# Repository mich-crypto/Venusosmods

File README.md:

# Venus OS mods: tank sensors and fridge for the camper van

Drivers that make devices Venus OS does not support show up as normal tanks
and temperature sensors in the Remote Console, on VRM, and on D-Bus (and so
on Modbus-TCP/MQTT):

| Device | D-Bus service(s) | Shown as |
|---|---|---|
| Mopeka Check **Standard / XL** (original, not Pro) | `com.victronenergy.tank.mopeka_standard` | LPG tank |
| Self-built **I/O extension** (ESP32-S3): hydrostatic fresh water sensor, grey tank rods, temperature probes | `com.victronenergy.tank.esp32_hydro`, `.tank.esp32_hydro_grey` (+ `.temperature.esp32_hydro_temp`, `.digitalinput.*` alarms) | fresh-water and waste-water tank (+ temperatures, frost / grey tank full alarms) |
| 12 V compressor **fridge** with the Alpicool Bluetooth controller (confirmed with a Hyckes dual-zone fridge) | `com.victronenergy.temperature.fridge_zone1` / `_zone2` | fridge / freezer temperature |

## Install (one command)

Open an SSH session to the Pi as `root` (the Termius app on an iPad works) and paste:

```sh
wget -qO- https://raw.githubusercontent.com/mich-crypto/Venusosmods/master/get.sh | sh
```

It downloads the mods, checks the Pi, switches on the **settings page** and prints its address and
password. Open that address on your phone, press **Unlock** and follow the **setup guide**: it finds your
gas sensor, fridge and I/O extension over Bluetooth, adds them to Venus OS and tells you where to find them.
Run the same command again any time to update; your settings are kept.

More: the [step-by-step guide](docs/GUIDE.md) (building the I/O extension, wiring, manual setup), also as a
printable **[PDF](docs/Venus-OS-Mods-Guide.pdf)**.

## Layout

```
data/                              -> copied to /data on the Pi
  shared_drivers/
    venus_service.py               shared layer: VenusDevice, TankDevice, TemperatureDevice, BleDriver
    ble_scanner.py                 passive BLE listener via BlueZ D-Bus (GLib loop, no bleak)
    ble_gatt.py                    BLE GATT client via BlueZ D-Bus (for the fridge)
    mopeka_std_parser.py           decoder: Mopeka Standard advertisements
    esp32_hydro_protocol.py        decoder: ESP32 advertisement (shared spec with the firmware)
    alpicool_protocol.py           decoder: fridge frames
    mopeka_venus.py                driver: Mopeka  -> tank
    esp32_hydro_tank.py            driver: ESP32   -> tank (+ temperature), Bluetooth check-in (Wi-Fi mode, firmware version)
    esp32_ota.py                   I/O extension firmware update from the Pi (Bluetooth, or HTTP on the van Wi-Fi)
    fridge_venus.py                driver: fridge  -> temperature per zone
    web_ui.py + web/index.html     settings page on port 8088: setup guide, calibration popups, drivers, dbus-serialbattery
    devices.py                     recognises Mopeka / fridge / ESP32 I/O extensions in a Bluetooth scan
    rawlog.py                      rolling log of the raw sensor bytes (shown on the Debug tab)
    starlink_hub.py                polls the dish, ping, speed tests, WAN IP, Telegram sending
    notifier.py                    Telegram notifications: battery, alarms, geofence, frost, Orion XS
    netmon.py                      energy, data use, outage and test bookkeeping (JSON store)
    starlink.py                    Starlink dish status (gRPC-web, hand-made protobuf reader)
    battery_debug.py               battery history for the graphs (cells, current, temperatures)
    config_tools.py                config.ini parsing, validation and safe writing for the page
    diagnostics/
      test_venus_compatibility.py  read-only pre-flight check, PASS/WARN/FAIL, optional BLE scan
      fridge_probe.py              does my fridge speak the supported protocol?
      starlink_probe.py            does the Starlink dish answer, and do we understand it?
    config.ini.example
    install.sh / uninstall.sh
  etc/init.d/<service>/run         daemontools services (+ log/run)
firmware/esp32_hydro_tank/         Arduino sketch for the ESP32-S3 (calibration via serial or its own Wi-Fi page)
firmware/bin/                      ready-made firmware for the browser flasher and the page's update
tools/tank_table.py                height->litres table from tank dimensions
tools/tank_wheelarch.py            filling chart of the wheel-arch tank (docs/tank/tank-drawing.jpg)
docs/                              guide, wiring, calibration
tests/                             unit tests + D-Bus integration test with simulated sensors
```

The layers are separate. Parsers (pure Python, no D-Bus) turn bytes into
readings. Devices publish one Victron D-Bus service each. Drivers connect
the two, one process per sensor. A new sensor type needs a parser and a
small driver; everything else is shared.

## Design decisions and review points

| Topic | How it is handled |
|---|---|
| Mopeka Standard | `mopeka-iot-ble` only decodes the Pro series. The Standard (company id 0x000D) decoder is a port of ESPHome's `mopeka_std_check`. |
| asyncio vs GLib | No bleak. BlueZ publishes advertisements and GATT on the system D-Bus, so everything runs in the GLib loop vedbus needs. No threads, no `pip install`, survives Venus OS updates. |
| Units | Config in litres. D-Bus `/Capacity` and `/Remaining` in m³ (60 L → 0.06), `/Level` in %. |
| Fluid types | Victron enum: 0 fuel, 1 fresh water, 2 waste water, 5 black water, 8 LPG, 11 raw water. |
| Metadata | velib_python `add_mandatory_paths` (Mgmt/*, DeviceInstance, ProductId, ProductName, Connected...), `/CustomName`, `/Status`. Each service is registered only after all its paths exist (`register=False` + `register()`). |
| Device instance | Stored in localsettings `/Settings/Devices/<id>/ClassAndVrmInstance`, which also resolves clashes. Stable across reboots, changeable in the GUI. |
| Several services | Each service has its own private D-Bus connection (vedbus object paths are per connection) and a unique, stable name from config. |
| velib path | Searched in `ext/velib_python`, `dbus-systemcalc-py` and `/opt/victronenergy/*/ext/velib_python`. The diagnostics report which one is used. |
| Sensor health | Per-device last-seen time. After `timeout`: `/Connected` = 0, `/Status` = disconnected, values set to invalid. Recovers on the next valid reading. Sensor faults show as `/Status` error, never as "empty". |
| Temperature | The tank `/Temperature` path is documented for Mopeka only, so the ESP32 water temperature is optionally also published as its own `com.victronenergy.temperature` service. DS18B20: CRC is checked, 85 °C power-on values are rejected, and the value is dropped after 3 bad reads. |
| Shutdown | SIGTERM (`svc -d`) is handled: the fridge connection is closed cleanly. |
| Persistence | Services in `/data/etc/init.d`, linked into `/service` and re-linked at boot by `/data/rc.local`. |
| Config format | INI rather than JSON: it can have comments and is easier to edit with `nano` over SSH. Checked by the diagnostics (MAC format, unique services, value types). |
| Non-square tank | Height→litres table measured by filling in steps (serial commands, stored in ESP32 flash) or calculated from dimensions with `tools/tank_table.py`. |

## Tests

```sh
python3 -m unittest discover tests -v
```
These test the decoders (including frames captured from real fridges) and the
driver logic with fake D-Bus objects, so they run on any PC.

`tests/integration_dbus.py` runs all three real drivers with the real
velib_python on a private D-Bus. A fake BlueZ sends Mopeka/ESP32
advertisements and plays a dual-zone fridge over GATT, and the test checks
every published value plus the clean shutdown:
```sh
git clone https://github.com/victronenergy/velib_python /tmp/velib_python
VELIB=/tmp/velib_python dbus-run-session -- python3 tests/integration_dbus.py
```

The firmware compiles warning-free on Arduino-ESP32 2.0.17 (Bluedroid) and
3.3.x (NimBLE).

Verified on the real installation (Venus OS 3.79, Raspberry Pi): the
diagnostics, Mopeka Standard decoding, and reading a Hyckes dual-zone fridge.
On the Pi's built-in Bluetooth, a GATT connection fails ("Busy") while any
process scans, so the fridge driver pauses the other drivers' scanning for
its few seconds of each read (`/tmp/venusosmods-ble-pause`). Still to verify:
the GUI/VRM display, and the ESP32 sender once it is built.

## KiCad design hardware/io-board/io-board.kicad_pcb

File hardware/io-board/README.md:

# I/O board – KiCad project (rev 0.4, routed, audited, JLCPCB parts – prototype)

KiCad 7 project for the board described in [docs/io-board.md](../../docs/io-board.md) and
[docs/io-board-schematic.md](../../docs/io-board-schematic.md). Open `io-board.kicad_pro` in
KiCad 7 or newer.

| File | What |
|---|---|
| `fab/io-board-gerbers.zip` | **Send this to the board maker:** Gerbers (2 layers, mask, paste, silkscreen, outline) and Excellon drill files (PTH and NPTH separate) |
| `fab/jlc/io-board-bom-jlc.csv`, `fab/jlc/io-board-cpl-jlc.csv` | **JLCPCB assembly files:** BOM with LCSC part numbers and placement list (164 parts; U92 not fitted), see "Ordering at JLCPCB" |
| `fab/io-board-pos.csv` | KiCad pick-and-place file (165 parts incl. U92, all on top; fiducials excluded) |
| `fab/io-board-bom.csv`, `io-board-bom.csv` | Parts list grouped by value and footprint (165 parts incl. U92; net ties, fiducials and the JP10 solder jumper are copper only) |
| `io-board.kicad_pcb` | Board 120 × 140 mm, 2 layers, **fully routed**: 0 unconnected, 0 DRC errors (see Checked) |
| `io-board.kicad_sch` | Schematic: 170 symbols (165 parts, the JP10 solder jumper, 4 net ties), grouped in 7 sections (power, ESP32, EBL, tanks, outputs, Truma + inputs, USB PD + sensors + expansion) |
| `io-board-schematic.pdf` | The schematic as PDF |
| `io-board.net` | Netlist exported by KiCad |
| `io-board.dsn` | The unrouted board for Freerouting (with the net classes) |
| `pcb-render-top.png`, `pcb-render-bottom.png` | Renders of the bare board as it comes from the fab (`sh tools/render.sh`) |
| `HANDOVER.md` | State, open items, tool chain and pitfalls for the next working session |
| `DESIGN-REVIEW.md` | Independent design audit: findings, calculations, what is and is not verified |
| `io_board.kicad_sym`, `sym-lib-table` | Project library with the PCA9615 symbol (not in the KiCad library) |
| `io_board.pretty`, `fp-lib-table` | Project footprints: RJ12 Connfly DS1133-S60 (6P6C), SK6812MINI-HS |
| `tools/` | Scripts: generate schematic and board from `parts.py`, rules, routing import, finishing, BOM, fab files |

**Order:** 2 layers, 1.6 mm FR-4, 1 oz (35 µm) copper, min. track/gap 0.15 mm, min. drill 0.3 mm,
any solder mask colour, **ENIG** finish (flat pads for the LGA-16, DFN-4 and 0.5 mm parts),
one internal routed slot (1 mm, around the SHT40).

## Checked

* **DRC (KiCad 7, with the KiCad libraries): 0 errors, 0 unconnected pads.** 38 warnings remain,
  all accepted: 31 × silkscreen past the board edge (the pluggable terminal blocks, RJ sockets,
  front-edge buttons and the ESP32 antenna overhang on purpose), 5 × the small J5 pin names touch
  the D1/D4 outline, 1 × silkscreen over a pad (removed in the Gerbers), 1 × ESP32 footprint
  differs from the library (thermal vias 0.3 mm, the 2-layer fab minimum).
* **Every pad carries the net `tools/parts.py` gives it** (525 pads compared), every footprint is
  linked to its schematic symbol, JLCPCB BOM and placement list agree (164 parts).
* KiCad reads the schematic and exports the netlist: 170 components, 120 named nets; the only
  one-pin nets are pins left open on purpose (spare ESP32 pins, sensor pins not used, SBU, LED DOUT).
* Electrical rules checked on KiCad's netlist: no two outputs on one net, every power input fed
  (power flags on GND, V12_SYS, V12_AUX, LIN_VBAT and the supplies).
* All footprints are linked to their symbols (Tools → Update PCB from Schematic works).
* No footprints overlap; all inside the outline (the ESP32 antenna keep-out sits at the back edge).
* Silkscreen: only small reference designators (placed so none overlaps a pad or another text),
  pin names next to every terminal block (J5: AUX+, GND, CP+, GND; J11: O1 C/NO/NC;
  J12: O2 C/NO/NC; J10: COM, IN1–IN3); part values are on the Fab layer only.
* KiCad 7's command line has no ERC: run **Inspect → Electrical Rules Checker** once in the GUI
  if you change the schematic.

## Before ordering

1. **Truma RJ12:** confirm pin 3 = LIN, pin 5 = GND with a meter; use a 1:1 cable.
2. **PCA9615 pinout:** checked against the NXP datasheet (Rev. 2, Table 3) and corrected (see below).
3. **Connector orientation:** all connectors open towards the edge they sit on (J5, J11, J12
   left; J8, J9, J3, J10 right; J1, J4, J6, J7 front). **J8/J9 (RJ12) use a footprint derived from
   KiCad's RJ14 Connfly DS1133** (6 contacts instead of 4): compare it with the Connfly drawing
   (LCSC C77859) – if the contact stagger were mirrored, LIN would arrive on pin 4.
4. **Front plate parts:** the 12 V ON/OFF buttons (Alps SKHHLQA010, right-angle, 8.35 mm stem,
   about 3 mm past the board edge) reach through holes in the front plate; the green "12 V on"
   LED (0603) and the RGB status LED sit at the edge and need light pipes in the plate.
5. **USB-C tablet charging:** a ready-made 12 V → USB-C PD 30 W module on J2 (its socket in the
   front plate), switched by Q80; no PD chip on this board.
6. **Tilt sensor:** order the **LIS3DH** (LGA-16 3 × 3, as on the board). The LIS2DH12 is LGA-12
   2 × 2 and does not fit this footprint.
7. **Stock:** JLCPCB stock was checked on 2026-11-28 (numbers in `tools/lcsc.py`); the BOM upload
   shows any line that ran out. U92 (PCA9615) is not fitted – solder it later for expansion boards.
8. **Plugs:** the pluggable terminal blocks need their plugs (not assembled): 1 × KF2EDGK-5.0-4P
   (C440871), 2 × KF2EDGK-5.0-3P (C440870), 1 × KF2EDGK-3.5-4P (C440849) – order from LCSC.
9. Order one prototype first.

## Ordering at JLCPCB

1. **PCB:** upload `fab/io-board-gerbers.zip`. 2 layers, 1.6 mm, 1 oz, **ENIG**, any colour; the
   board has one internal routed slot (SHT40) – JLCPCB detects it from the outline.
2. **Assembly:** "PCB Assembly", top side, **Standard** PCBA (the board has through-hole parts:
   relays, terminal blocks, RJ sockets, Micro-Fit, TSR-1, buttons). Upload
   `fab/jlc/io-board-bom-jlc.csv` and `fab/jlc/io-board-cpl-jlc.csv`.
3. **Check the placement preview** part by part, especially the rotation and pin 1 of: U3
   (ESP32), U90 (LIS3DH), U91 (SHT40), U60, U5–U8/U71–U73 (opto/photoMOS), D1–D4,
   D13, D14, D61, the LEDs and the RJ/USB connectors. The CPL uses KiCad's rotations; JLCPCB
   corrects them in the preview where their library differs.
4. Confirm the parts JLCPCB marks as "extended" (one-off fee per part type) and the through-hole
   parts (soldering fee).

## Checked against datasheets

Pinouts read from the manufacturers' datasheets (NXP PCA9615 Rev. 2, Diodes AP7361C, AOS AO3401A,
TI INA180 SBOS741H, Omron G5LE, SK6812MINI-E Rev. 02) and from KiCad's library symbols.

**Fixed:**

| Part | Problem | Fix |
|---|---|---|
| U92 PCA9615 | Pins 2–9 were wrong: pin 5 (VSS) was on +3.3 V, SDA/SCL/EN and the differential pins swapped | Pinout per Table 3: 1 VDD(A), 2 SDA, 3 EN, 4 SCL, 5 VSS, 6 DSCLM, 7 DSCLP, 8 DSDAP, 9 DSDAM, 10 VDD(B) |
| U2 AP7361C-33E | "-33E" is the SOT223 package; the board had a SOT-89-3 footprint (the SOT89 version has 5 pins) | Footprint SOT-223-3 (tab = GND) |
| Q80 AO3401A | Gate rated ±12 V, but Q81 pulled it to GND: VGS = −12…−14.6 V | R83 100 k in series: VGS = −V/2 (≈ −7 V), RDS(on) < 60 mΩ at −4.5 V |
| D5 status LED | Value SK6812MINI-E (3.2 × 2.8, pin 1 VDD, 4 DIN) on the SK6812MINI footprint and pinout (3.5 × 3.5, pin 4 VDD) | Value SK6812MINI, to match footprint and pinout |
| D5 data level | SK6812MINI: VIH 3.4 V at VDD 5 V (datasheet); the ESP32 drives 3.3 V | LED fed through D6 (1N4148W): VDD ≈ 4.3 V, VIH ≈ 2.9 V (scales with VDD) |
| D4 TVS | SMBJ24CA clamps at 38.9 V, above C1 (35 V) and the TSR-1 input (36 V) | SMBJ18A (stand-off 18 V, clamps 29.2 V), band to V12_SYS |
| R50/R51 shunts | 0.05 Ω at 5 A = 1.25 W; a standard 2512 is 1 W | Value "0.05 2W" (2 W or 3 W metal strip 2512) |
| U90 | BOM said LIS2DH12, which does not fit (see 6.) | Value LIS3DH |

**Verified, no change:** INA180A3 (pinout A: 1 OUT, 2 GND, 3 IN+, 4 IN−, 5 VS; common mode up to
26 V), G5LE-1 (coil 2–5, COM 1, NO 3, NC 4; 8 A at 30 VDC against 5 A used), TJA1021T, USBLC6-2SC6,
SHT40, LMV331, AO3400A, TSR 1-2450 (KiCad symbols). No mains voltage on the board: the EBL "mains"
wire is an ≈ 8 V indicator, so no high-voltage clearances are needed.

**Still for you to check (not possible from here):**

* **Stock:** see Before ordering, 7.
* **Pressure sensor:** the ADC input has no divider, so it is for the 0–3.3 V sensor (QDY30A). A
  0.5–4.5 V sensor needs a divider at R21/R22.
* **AO3401A turn-off:** R80/R83 make Q80 switch slowly (100 k); fine for the PD module, not for PWM.

## Rev 0.4: parts JLCPCB stocks

Every part is now one JLCPCB/LCSC stocks (2026-11-28); the substitutes and the fixes found
while reading their datasheets:

| Ref | Rev 0.3 | Rev 0.4 (LCSC) | Notes |
|---|---|---|---|
| K1, K2 | Omron G5LE-1 12 V (no stock) | Songle SRD-12VDC-SL-C (C30431) | 10 A 250 VAC / 28 VDC; same pin functions (1 COM, 2–5 coil, 3 NO, 4 NC), SRD footprint |
| J5 (10-way push-in) | Phoenix PT 1,5 | J5 4-way (AUX+, GND, CP+, GND), J11 / J12 3-way (output 1 / 2 C, NO, NC): pluggable KF2EDGR-5.0 (C441195, C441194) | 15 A; plugs ordered separately |
| J10 | Phoenix PT 1,5 3.5 mm | KF2EDGR-3.5-4P (C441173) | pluggable |
| J8, J9 | Amphenol RJ12 | Connfly DS1133-S60BPX (C77859) | footprint derived from KiCad's DS1133 RJ14 – check (Before ordering 3) |
| J3 | Amphenol RJ45 | Connfly DS1128-09-S8B8S (C77851) | shielded, shield to GND |
| F2, F4, F5, F7 | blade holder / 1812 fuses | Littelfuse Nano2 0451010/005/004 (C44479, C48467, C27515) | soldered SMD fuses, 125 V |
| SW1, SW2 | TL3342 | XKB TS-1187A-B-A-B (C318884, basic) | |
| SW3, SW4 | PTS645VL83 | Alps SKHHLQA010 (C125034) | right-angle, 8.35 mm stem |
| D9 | 3 mm right-angle LED | green 0603 (C12624) at the front edge | light pipe |
| D5 | SK6812MINI (no stock) | SK6812MINI-HS (C2922787) | **different pin positions** – own footprint from the OPSCO pad drawing |
| JP1, JP2 | 0 Ω 2512 | 1 mΩ 2 W 2512 (C2904226) | 44 A rated |
| C1 | 47 µF 35 V 1210 | 10 µF 50 V X7R 1210 (C138687) | |
| Q3 | IPD90P04P4L-04 (no stock) | AOS AOD4185 (C400894) | −40 V, 15 mΩ: 0.4 W at 5 A, 1.5 W at 10 A (RθJA 50 °C/W) |
| U92 | PCA9615 (no stock) | **not fitted** | termination and ESD stay; fit for expansion boards |
| **U5, U6** | AQY212EH on SO-4 footprint | **SMDIP-4** footprint | **error since rev 0.1:** the AQY212EH is a DIP4 part; its SMD version (EHAX, C29276) has gull-wing leads |

Also: pin names of the left terminal blocks turned 90° between the blocks and the relays;
`finish_routes.py` now routes wide nets first, never makes a pad stub narrower than the pad
allows, and respects pads' own clearances (fiducials).

## Rev 0.3: audit findings fixed

The independent audit ([DESIGN-REVIEW.md](DESIGN-REVIEW.md)) found three HIGH and six MEDIUM
issues in rev 0.2. All are resolved in rev 0.3 and re-measured on the routed board:

| Finding | Fix in rev 0.3 | Re-measured |
|---|---|---|
| H1 decoupling 15–109 mm from the pins, no bypass at INA180/LMV331 | Capacitors placed by a near-pin rule (`NEAR` in `pcb.py`); C9 (TSR-1 out), C94–C97 (INA180/LMV331) added | every decoupling cap 2.1–4.5 mm from its pin |
| H2 12 V AUX without reverse-polarity / transient protection | Q3 IPD90P04P4L-04 P-MOSFET (D13 12 V gate clamp, R7) after F2; D14 SMBJ15A on V12_AUX | reversed AUX: Q3 off; clamp 24.4 V < INA180 26 V, < 30 V MOSFETs |
| H3 front-plate controls behind the plugs | Right-angle buttons SW3/SW4 and LED D9 on the front edge, D5 at the edge with a light pipe; ST1–ST3 and USB-C packed to the left | actuators 5.5 mm, D9 lens 1.6 mm past the edge |
| M1 LMV331 input range at 3.3 V | U12/U22 on +5 V (VICR to 4.2 V), outputs still pulled to 3.3 V | – |
| M2 input resistors overloaded at 30 V | R71–R73 4.7 k **1206** (250 mW); inputs specified 9–30 V | 169 mW at 30 V |
| M3 input jumper spec | Spec corrected: 9–30 V = on, COM to GND by JP10, dry contacts from +12 V | – |
| M5 no ESD on the RJ45 lines | U93 ESDA6V1-5SC6 on DSDA±, DSCL±, EXP_INT | – |
| M6 HASL on fine pitch | Order ENIG | – |
| L1 no fiducials | FID1–FID3 (1 mm, excluded from pick-and-place) | – |
| L5 documents contradict the board | io-board.md and io-board-schematic.md updated | – |
| L6 no SHT40 slot | 1 mm U-shaped routed slot around the SHT40 island, keep-out on the slot | – |
| 5 A vias | Via clusters with copper squares at every 5 A layer change (`via_room.py`, `finish.py`) | 4–8 vias each |

Not changed: M4 (long USB lines – the USB-C must stay at the front edge and the ESP32 antenna at
the back; full-speed USB tolerates it), L2 (USB-C footprint hole spacing, same net), L3 (TSR-1
back-feed from USB: check the Traco datasheet), L4 (J5 GND must be wired – documented).

## Engineering review (rev 0.2)

Second full check: every pin against the manufacturer's datasheet, every net name, every
current path against its track, pour and vias. Datasheets read: NXP PCA9615 Rev. 2, NXP TJA1021
Rev. 9, ST LIS3DH Rev. 1, SK6812MINI Rev. 01, SK6812MINI-E Rev. 02, Diodes AP7361C, AOS AO3401A,
TI INA180 (SBOS741H), Omron G5LE.

**Found and fixed in rev 0.2:**

| # | Problem | Consequence | Fix |
|---|---|---|---|
| 1 | No termination / idle bias on the dI2C pairs (PCA9615 datasheet Fig. 5/7: R1-R2-R1 at each cable end) | The PCA9615 hot-swap logic only connects to a bus with valid termination: the expansion port would never work | R94–R99: 620 Ω to +5 V, 120 Ω across, 620 Ω to GND on DSCL and DSDA (100 Ω termination, D+ above D−). The expansion module needs the same network at its end |
| 2 | LIS3DH INT1 is push-pull only (CTRL_REG6 has polarity, no open-drain bit) and shared I2C_INT with the expansion INT line | An expansion module pulling INT low fights the sensor driving it high | Split: TILT_INT (LIS3DH → GPIO47), EXP_INT_MCU (RJ45 pin 7 via R92 100 Ω, 10 k pull-up R93 → GPIO40, open drain) |
| 3 | OUT1_C (JP1 → relay K1 COM, 5 A) changed layer through 2 vias of 0.3 mm (≈ 1.8 A each) | Via overheating at full load | 7 vias with copper squares on both layers; the other 5 A layer changes have 5–8 vias; V12_AUX 6–9 |
| 4 | TRUMA_12V and EXP_12V (1 A PTC, trips at ≈ 2 A) only as 0.3 mm tracks | Warm tracks before the PTC trips | Pours along both nets (up to 1.5 mm each side) |
| 5 | Fuse values without voltage rating | Wrong parts could be ordered | F1 0.5 A 30 V PTC, F3 50 mA 15 V PTC, F4/F5 5 A 32 V fast, F6/F8 1 A 30 V PTC, F7 4 A 32 V fast, F2 10 A mini blade |
| 6 | ESP32 module variant not pinned down | The -N8R8/-N16R8 use GPIO35–37 for octal PSRAM (EBL ON/OFF/12 V sense here) | Value note: ESP32-S3-WROOM-1-**N8** only |

**Checked, correct:**

* **Pinouts against the datasheets:** PCA9615 (Table 3), TJA1021 (1 RXD open drain with 10 k
  pull-up, 2 SLP_N with 100 k pull-down, 3 WAKE_N to VBAT through 10 k, 4 TXD, 5 GND, 6 LIN, 7 VBAT,
  8 INH open), LIS3DH (1 VDD_IO, 4 SCL, 6 SDA, 7 SA0 → GND = 0x18, 8 CS → 3.3 V = I2C, 10 RES → GND,
  11 INT1, 14 VDD), SK6812MINI (1 DOUT, 2 VSS, 3 DIN, 4 VDD), AP7361C-33E SOT223 (1 IN, 2/tab GND,
  3 OUT), INA180A3 pinout A, AO3400A/AO3401A (1 G, 2 S, 3 D), G5LE (coil 2–5, COM 1, NO 3, NC 4),
  USBLC6-2SC6, SHT40, TSR 1-2450, ESP32-S3-WROOM-1 (by pin name through KiCad's symbol; strapping
  GPIO0/3/45/46 not driven, USB D−/D+ on GPIO19/20, battery divider on ADC1).
* **Diode and LED polarity** (KiCad pin 1 = cathode = band/pad 1): D1/D2/D3/D61 series diodes,
  D4 SMBJ18A band to V12_SYS, flyback D11/D12 cathode to +12 V, input diodes D71–D73, zeners
  D7/D8 reverse biased, LEDs D9/D41/D42 anode to the resistor.
* **Operating points:** relay drive 3.3 V on AO3400A (VGS(th) ≤ 1.45 V); photoMOS LED 6 mA
  (AQY212EH needs ≤ 3 mA); EBL "12 V on" opto 1.3 mA at 12 V, "mains" opto 2 mA at 8 V;
  inputs 2.1 mA; battery divider 15 V → 2.7 V; Output "on" threshold 0.148 V / (100 × 0.05 Ω)
  = 30 mA; Q80 VGS ≈ −7 V with R80/R83; USB-C CC 5.1 k on both.
* **Net names** say what the net is (OUT1_C/NO/NC, SH1_P/N + Kelvin SH1_SP/SN, EBL_ON/OFF,
  TILT_INT, EXP_INT_MCU, …); no net is left with a name that does not match its function.
* **Every pad on the board carries the net parts.py gives it** (500 pads compared), every
  footprint is linked to its schematic symbol.
* **Current paths:** all 5–10 A nets are 2 mm tracks (only short neck-downs at small pads), with
  pours where there is room; R50 → JP1 runs on one layer; GND is connected by tracks alone and
  additionally poured on both layers.

**Not changed, worth knowing:**

* USB D+/D− are long (≈ 160–175 mm, 2–4 vias): fine for 12 Mbit/s full speed, keep the
  programming cable short.
* SK6812MINI data at 3.3 V against VIH ≈ 2.9 V (VDD 4.3 V): about 0.4 V margin.
* The expansion module must carry the same 620/120/620 Ω network at its PCA9615.

## Layout and routing

| Class | Track | Clearance | Nets |
|---|---|---|---|
| HighCurrent | 2.0 mm | 0.3 mm | 12 V AUX, both outputs (C/NO/NC, shunts, fuses, JP1/JP2), USB PD supply |
| Power | 0.3 mm | 0.15 mm | 12 V system, +5 V, +3.3 V, GND, LIN supply, sensor and CP plus 12 V, relay coils |
| Default | 0.25 mm | 0.15 mm | all signals, the INA180 sense lines |

* **12 V AUX (F2, 10 A):** reverse-polarity MOSFET Q3 and TVS D14 after the fuse; besides the 2 mm tracks, copper pours along every V12_AUX track
  (up to 3 mm each side, both layers) carry the trunk from F2 to the output fuses, F7 and relays.
* **Current sense:** the INA180s measure the shunts through net ties (Kelvin taps NT11–NT22), so
  the 5 A current does not flow in their sense lines.
* **GND:** routed as a net (tracks and vias) and in addition a copper pour on both layers; small
  pads connect solidly, through-hole pads with thermal spokes. The ESP32 antenna end has no copper.
* **Heat:** U2 (SOT223) sits with its tab in the GND pour; R50/R51 and Q80 have 2 mm tracks on both
  pads; the relays and fuses have the V12_AUX pours.
* **Silkscreen:** "EXPANSION 12V / NO ETHERNET" at the RJ45 (pins 1–2 carry 12 V).
* The clearances are 0.15 mm so tracks reach the 0.5 mm pitch pins (LIS3DH, PCA9615, USB-C);
  for 12 V a gap of 0.1 mm is enough (IPC-2221). The hole clearance is 0.19 mm because the USB-C
  footprint (GCT USB4105) has its pegs 0.194 mm from its GND pads.

How the board was routed (to repeat after changes, with KiCad 7's Python and Freerouting 1.9.0;
Freerouting needs a display, e.g. `xvfb-run`):

1. `python3 tools/pcb.py && python3 tools/rules.py && python3 tools/zones.py` (in a scratch folder
   with `io-board.kicad_pro`, see Regenerating), then remove from `io-board.dsn` the `(plane GND …)`
   entries (GND is routed as a net) and the `(keepout "" (polygon signal …))` that KiCad writes for
   the SHT40 slot (it covers the whole island; the slot arms have their own keep-outs).
2. `java -jar freerouting-1.9.0.jar -de io-board.dsn -do io-board.ses -mp 100`
3. `python3 tools/import_ses.py io-board.kicad_pcb io-board.ses drc.rpt` (KiCad 7 imports .ses only
   in the GUI; this does it with the API).
4. Netlist changes after routing: edit `tools/parts.py`, then `python3 tools/apply_netlist.py`
   (regenerates the schematic, links footprints, sets pad nets, places new parts on free area).
   `python3 tools/move_near.py io-board.kicad_pcb REF:IC:PIN …` moves a part next to a pin on the
   routed board. `python3 tools/via_room.py io-board.kicad_pcb NET:x:y …` clears room for a via
   cluster at a crowded 5 A layer change. `python3 tools/stubs.py io-board.kicad_pcb` (exit tracks for the SHT40 pads past its keep-out),
   then `python3 tools/finish_routes.py io-board.kicad_pcb` routes whatever Freerouting left
   (grid A* with the net-class clearances) and removes dangling stubs.
5. `python3 tools/finish.py io-board.kicad_pcb`: pours on the 5–10 A and 1 A nets, via clusters,
   JP10 off the plane, fiducials out of the pick-and-place, footprint library names, RJ45 warning
   text, reference texts off other silkscreen, no copper islands, zones refilled.
6. `sh tools/fab.sh` writes `fab/`, `sh tools/render.sh` the renders.

## Regenerating

The schematic and the board are generated from `tools/parts.py`: change the netlist there and
run, with KiCad 7's Python (`pcbnew` module):

```
cd hardware/io-board/tools && python3 pcb.py && python3 rules.py && python3 zones.py
```

It writes `io-board.kicad_sch` and `io-board.kicad_pcb` into the current folder. Once routing
has started in KiCad, edit the KiCad files directly instead.

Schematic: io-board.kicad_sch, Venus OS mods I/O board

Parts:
C1: 10u/50V; C_1210_3225Metric
C2, C3: 22u; C_0805_2012Metric
C4, C6, C8, C20, C31, C32, C33, C34, C60, C90, C91, C92, C93, C94, C95, C96, C97: 100n; C_0603_1608Metric
C5, C9: 10u; C_0805_2012Metric
C7: 1u; C_0603_1608Metric
D1, D2: SS34; D_SMA
D3, D61: SS14; D_SMA
D4: SMBJ18A; D_SMB
D5: SK6812MINI-HS; LED_SK6812MINI-HS_3.7x3.5mm
D6, D11, D12, D71, D72, D73: 1N4148W; D_SOD-123
D7: 4V7; D_SOD-123
D8: 2V4; D_SOD-123
D9: green 0603; LED_0603_1608Metric
D13: BZT52C12; D_SOD-123
D14: SMBJ15A; D_SMB
D20, D21, D31, D32, D33, D34: ESD 5V; D_SOD-323
D41, D42: red; LED_0603_1608Metric
D60: PESD1LIN; D_SOD-323
F1: 0.5A 30V PTC; Fuse_1206_3216Metric
F2: 10A 0451010.MRL; Fuse_Littelfuse-NANO2-451_453
F3: 50mA 15V PTC; Fuse_1206_3216Metric
F4, F5: 5A 0451005.MRL; Fuse_Littelfuse-NANO2-451_453
F6, F8: 1A 30V PTC; Fuse_1812_4532Metric
F7: 4A 0451004.MRL; Fuse_Littelfuse-NANO2-451_453
J1: USB PROG; USB_C_Receptacle_GCT_USB4105-xx-A_16P_TopMnt_Horizontal
J2: PD module; PinHeader_1x02_P2.54mm_Vertical
J3: DS1128-09-S8B8S; RJ45_Connfly_DS1128-09-S8xx-S_Horizontal
J4: ST1 EBL; Molex_Micro-Fit_3.0_43045-0600_2x03_P3.00mm_Horizontal
J5: KF2EDGR-5.0-4P; PhoenixContact_MSTBA_2,5_4-G_1x04_P5.00mm_Horizontal
J6: ST2 FRESH; Molex_Micro-Fit_3.0_43650-0600_1x06_P3.00mm_Horizontal
J7: ST3 GREY; Molex_Micro-Fit_3.0_43650-0500_1x05_P3.00mm_Horizontal
J8, J9: DS1133-S60BPX; RJ12_Connfly_DS1133-S60_Horizontal
J10: KF2EDGR-3.5-4P; PhoenixContact_MC_1,5_4-G-3.5_1x04_P3.50mm_Horizontal
J11, J12: KF2EDGR-5.0-3P; PhoenixContact_MSTBA_2,5_3-G_1x03_P5.00mm_Horizontal
JP1, JP2: 1m 2W 2512 (C-feed link); R_2512_6332Metric
JP10: JP COM; SolderJumper-2_P1.3mm_Bridged_RoundedPad1.0x1.5mm
K1, K2: SRD-12VDC-SL-C; Relay_SPDT_SANYOU_SRD_Series_Form_C
NT11, NT12, NT21, NT22: NetTie; NetTie-2_SMD_Pad0.5mm
Q1, Q2: AO3400A; SOT-23
Q3: AOD4185; TO-252-2
Q80: AO3401A; SOT-23
Q81: 2N7002; SOT-23
R1, R41, R42, R43, R44, R59, R63, R80, R82, R83, R106, R206: 100k; R_0603_1608Metric
R2: 22k; R_0603_1608Metric
R3, R7, R15, R16, R21, R31, R32, R33, R34, R61, R62, R74, R75, R76, R93, R108, R208: 10k; R_0603_1608Metric
R4, R5: 5.1k; R_0603_1608Metric
R6, R10, R11: 330; R_0603_1608Metric
R12, R24, R58, R90, R91: 4.7k; R_0603_1608Metric
R13, R14, R107, R207: 2.2k; R_0603_1608Metric
R20, R23, R92: 100; R_0603_1608Metric
R22: 1M; R_0603_1608Metric
R30, R81, R105, R205: 1k; R_0603_1608Metric
R50, R51: 0.05 2W; R_2512_6332Metric
R71, R72, R73: 4.7k 0.25W; R_1206_3216Metric
R94, R96, R97, R99: 620; R_0603_1608Metric
R95, R98: 120; R_0603_1608Metric
SW1, SW2: TS-1187A-B-A-B; SW_Push_1P1T_XKB_TS-1187A
SW3, SW4: SKHHLQA010; SW_Tactile_SKHH_Angled
U1: TSR 1-2450; Converter_DCDC_TRACO_TSR-1_THT
U2: AP7361C-33E; SOT-223-3_TabPin2
U3: ESP32-S3-WROOM-1-N8; ESP32-S3-WROOM-1
U4: USBLC6-2SC6; SOT-23-6
U5, U6: AQY212EH; SMDIP-4_W9.53mm
U7, U8, U71, U72, U73: PC817; SMDIP-4_W9.53mm
U11, U21: INA180A3; SOT-23-5
U12, U22: LMV331; SOT-23-5
U60: TJA1021T/20; SOIC-8_3.9x4.9mm_P1.27mm
U90: LIS3DH; LGA-16_3x3mm_P0.5mm_LayoutBorder3x5y
U91: SHT40-AD1B; Sensirion_DFN-4_1.5x1.5mm_P0.8mm_SHT4x_NoCentralPad
U92: PCA9615DP; TSSOP-10_3x3mm_P0.5mm
U93: ESDA6V1-5SC6; SOT-23-6

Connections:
+3V3: C3.1, C5.1, C6.1, C90.1, C91.1, C92.1, C94.1, C96.1, R3.1, R15.1, R16.1, R20.1, R24.1, R59.1, R62.1, R74.1, R75.1, R76.1, R90.1, R91.1, R93.1, R108.1, R208.1, U2.3 (VO), U3.2 (3V3), U11.5 (V+), U21.5 (V+), U90.1 (VDD_IO), U90.8 (CS), U90.14 (VDD), U91.3 (VDD), U92.1 (VDDA), U92.3 (EN)
+5V: C2.1, C9.1, C93.1, C95.1, C97.1, D3.1 (K), D6.2 (A), F3.1, R94.1, R97.1, U1.3 (Vout), U2.1 (VI), U12.5 (V+), U22.5 (V+), U92.10 (VDDB)
BOOT: SW2.1, U3.27 (IO0)
CC1_PROG: J1.A5 (CC1), R4.1
CC2_PROG: J1.B5 (CC2), R5.1
DSCL_M: J3.5, R95.2, R96.1, U92.6 (DSCLM), U93.5 (IO4)
DSCL_P: J3.4, R94.2, R95.1, U92.7 (DSCLP), U93.4 (IO3)
DSDA_M: J3.6, R98.2, R99.1, U92.9 (DSDAM), U93.3 (IO2)
DSDA_P: J3.3, R97.2, R98.1, U92.8 (DSDAP), U93.1 (IO1)
EBL_12V: J4.3, R12.1, R14.1
EBL_12V_SENSE: R15.2, U3.30 (IO37), U7.4
EBL_MAINS: J4.4, R13.1
EBL_MAINS_SENSE: R16.2, U3.35 (IO42), U8.4
EBL_OFF: J4.1, SW4.1, U6.4
EBL_OFF_DRV: R11.1, U3.29 (IO36)
EBL_ON: J4.2, SW3.1, U5.4
EBL_ON_DRV: R10.1, U3.28 (IO35)
EN: C7.1, R3.2, SW1.1, U3.3 (EN)
EXP_12V: F8.2, J3.1, J3.2
EXP_INT: J3.7, R92.2, U93.6 (IO5)
EXP_INT_MCU: R92.1, R93.2, U3.33 (IO40)
FRESH_3V3: J6.5, R20.2
FRESH_5V: F3.2, J6.4
FRESH_PRESSURE: C20.1, R21.2, R22.1, U3.4 (IO4)
FRESH_P_RAW: D20.1 (A1), J6.2, R21.1
FRESH_TEMP: R23.2, R24.2, U3.5 (IO5)
FRESH_T_RAW: D21.1 (A1), J6.1, R23.1
GND: C1.2, C2.2, C3.2, C4.2, C5.2, C6.2, C7.2, C8.2, C9.2, C20.2, C31.2, C32.2, C33.2, C34.2, C60.2, C90.2, C91.2, C92.2, C93.2, C94.2, C95.2, C96.2, C97.2, D4.2 (A2), D5.2 (VSS), D9.1 (K), D14.2 (A2), D20.2 (A2), D21.2 (A2), D31.2 (A2), D32.2 (A2), D33.2 (A2), D34.2 (A2), D60.2 (A2), J1.A1 (GND), J1.A12 (GND), J1.B1 (GND), J1.B12 (GND), J1.S1 (SHIELD), J2.2, J3.8, J3.SH, J4.5, J5.2, J5.4, J6.3, J8.5, J9.5, JP10.2 (B), Q1.2 (S), Q2.2 (S), Q81.2 (S), R2.2, R4.2, R5.2, R7.2, R22.2, R41.2, R42.2, R43.2, R44.2, R58.2, R63.2, R82.2, R96.2, R99.2, R106.2, R206.2, SW1.2, SW2.2, SW3.2, SW4.2, U1.2 (GND), U2.2 (GND), U3.1 (GND), U3.40 (GND), U3.41 (GND), U4.2 (GND), U5.2, U5.3, U6.2, U6.3, U7.2, U7.3, U8.2, U8.3, U11.2 (GND), U12.2 (V-), U21.2 (GND), U22.2 (V-), U60.5 (GND), U71.3, U72.3, U73.3, U90.5 (GND), U90.7 (SDO/SA0), U90.10 (GND), U90.12 (GND), U91.4 (VSS), U92.5 (GND), U93.2 (GND)
GREY_COM: J7.5, R30.2
GREY_COM_DRV: R30.1, U3.17 (IO9)
GREY_ROD1: C31.1, R31.2, U3.39 (IO1)
GREY_ROD2: C32.1, R32.2, U3.38 (IO2)
GREY_ROD3: C33.1, R33.2, U3.7 (IO7)
GREY_ROD4: C34.1, R34.2, U3.12 (IO8)
IN1: R74.2, U3.19 (IO11), U71.4
IN1_A: R71.2, U71.1
IN1_D: D71.1 (K), R71.1
IN1_T: D71.2 (A), J10.2
IN2: R75.2, U3.20 (IO12), U72.4
IN2_A: R72.2, U72.1
IN2_D: D72.1 (K), R72.1
IN2_T: D72.2 (A), J10.3
IN3: R76.2, U3.21 (IO13), U73.4
IN3_A: R73.2, U73.1
IN3_D: D73.1 (K), R73.1
IN3_T: D73.2 (A), J10.4
IN_COM: J10.1, JP10.1 (A), U71.2, U72.2, U73.2
ISENSE1: U11.1, U12.1 (+)
ISENSE2: U21.1, U22.1 (+)
K1_COIL: D11.2 (A), D41.1 (K), K1.2, Q1.3 (D)
K1_LED: D41.2 (A), R107.2
K2_COIL: D12.2 (A), D42.1 (K), K2.2, Q2.3 (D)
K2_LED: D42.2 (A), R207.2
LED_DATA: R6.1, U3.25 (IO48)
LED_DIN: D5.3 (DIN), R6.2
LED_VDD: C8.1, D5.4 (VDD), D6.1 (K)
LIN: D60.1 (A1), J8.3, J9.3, U60.6 (LIN)
LIN_RXD: R62.2, U3.10 (IO17), U60.1 (RXD)
LIN_SLP: R63.1, U3.23 (IO21), U60.2 (~SLP)
LIN_TXD: U3.11 (IO18), U60.4 (TXD)
LIN_VBAT: C60.1, D61.1 (K), R61.1, U60.7 (VBAT)
LIN_WAKE: R61.2, U60.3 (~WAKE)
N_12V_A: D7.2 (A), U7.1
N_12V_Z: D7.1 (K), R12.2
N_LED12: D9.2 (A), R14.2
N_MAINS_A: D8.2 (A), U8.1
N_MAINS_Z: D8.1 (K), R13.2
OUT1_C: J11.1, JP1.2 (B), K1.1
OUT1_DRV: R105.1, U3.31 (IO38)
OUT1_NC: J11.3, K1.4
OUT1_NO: J11.2, K1.3
OUT1_SENSE: R108.2, U3.22 (IO14), U12.4
OUT2_C: J12.1, JP2.2 (B), K2.1
OUT2_DRV: R205.1, U3.32 (IO39)
OUT2_NC: J12.3, K2.4
OUT2_NO: J12.2, K2.3
OUT2_SENSE: R208.2, U3.6 (IO6), U22.4
PD_12V: J2.1, Q80.3 (D)
PD_EN_G: Q81.1 (G), R81.2, R82.1
PD_G: Q80.1 (G), R80.2, R83.2
PD_G_DRV: Q81.3 (D), R83.1
PD_SUPPLY: F7.2, Q80.2 (S), R80.1
Q1_G: Q1.1 (G), R105.2, R106.1
Q2_G: Q2.1 (G), R205.2, R206.1
Q3_G: D13.2 (A), Q3.1 (G), R7.1
ROD1_RAW: D31.1 (A1), J7.4, R31.1, R41.1
ROD2_RAW: D32.1 (A1), J7.3, R32.1, R42.1
ROD3_RAW: D33.1 (A1), J7.2, R33.1, R43.1
ROD4_RAW: D34.1 (A1), J7.1, R34.1, R44.1
SCL: R91.2, U3.9 (IO16), U90.4 (SCL/SPC), U91.2 (SCL), U92.4 (SCL)
SDA: R90.2, U3.8 (IO15), U90.6 (SDA/SDI/SDO), U91.1 (SDA), U92.2 (SDA)
SH1_N: JP1.1 (A), NT12.1, R50.2
SH1_P: F4.2, NT11.1, R50.1
SH1_SN: NT12.2, U11.4 (-)
SH1_SP: NT11.2, U11.3 (+)
SH2_N: JP2.1 (A), NT22.1, R51.2
SH2_P: F5.2, NT21.1, R51.1
SH2_SN: NT22.2, U21.4 (-)
SH2_SP: NT21.2, U21.3 (+)
ST1_12V: F1.1, J4.6, R1.1
ST1_12V_F: D1.2 (A), F1.2
TILT_INT: U3.24 (IO47), U90.11 (INT1)
TR1: J8.1, J9.1
TR2: J8.2, J9.2
TR4: J8.4, J9.4
TR6: J8.6, J9.6
TRUMA_12V: F6.2, J5.3
U5_LED: R10.2, U5.1
U6_LED: R11.2, U6.1
USB_DM: J1.A7 (D-), J1.B7 (D-), U3.13 (IO19), U4.1 (I/O1), U4.6 (I/O1)
USB_DP: J1.A6 (D+), J1.B6 (D+), U3.14 (IO20), U4.3 (I/O2), U4.4 (I/O2)
USB_PD_EN: R81.1, U3.34 (IO41)
V12_AUX: D2.2 (A), D11.1 (K), D12.1 (K), D13.1 (K), D14.1 (A1), F4.1, F5.1, F6.1, F7.1, F8.1, K1.5, K2.5, Q3.3 (S), R107.1, R207.1
V12_AUX_F: F2.2, Q3.2 (D)
V12_AUX_IN: F2.1, J5.1
V12_SYS: C1.1, D1.1 (K), D2.1 (K), D4.1 (A1), D61.2 (A), U1.1 (Vin)
VBAT_SENSE: C4.1, R1.2, R2.1, U3.18 (IO10)
VBUS_PROG: D3.2 (A), J1.A4 (VBUS), J1.A9 (VBUS), J1.B4 (VBUS), J1.B9 (VBUS), U4.5 (VBUS)
VREF: R58.1, R59.2, U12.3 (-), U22.3 (-)

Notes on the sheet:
1 · Power
2 · ESP32-S3, USB-C programming, status LED
3 · EBL 119 (ST1) and front plate buttons
4 · Tanks: ST2 fresh water, ST3 grey water
5 · Output 1 and Output 2 (relays with current sense)
6 · Truma LIN, CP plus 12 V, inputs
7 · USB PD module, tilt + humidity sensors, RJ45 expansion
Power flags

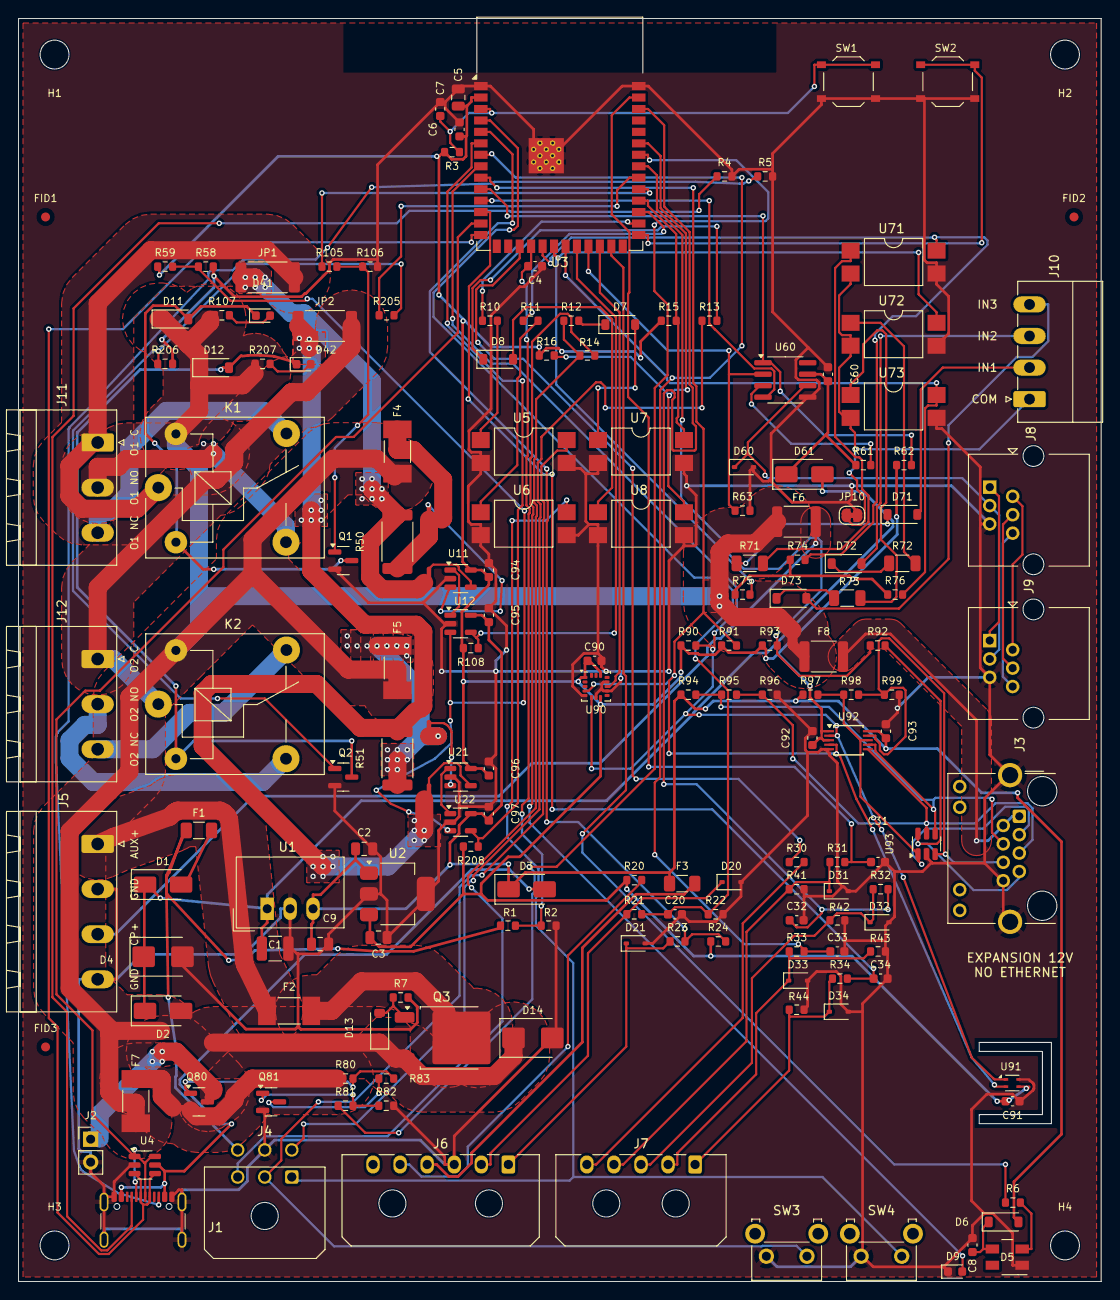
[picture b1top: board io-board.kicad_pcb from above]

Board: 2 copper layers, 120.0 x 140.0 mm, 177 parts (0 on the bottom side), 119 nets.

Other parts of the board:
FID1, FID2, FID3: Fiducial; Fiducial_1mm_Mask2mm
H1, H2, H3, H4: M3; MountingHole_3.2mm_M3

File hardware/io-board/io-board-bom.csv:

Qty,References,Value,Footprint,Symbol
1,J4,ST1 EBL,Connector_Molex:Molex_Micro-Fit_3.0_43045-0600_2x03_P3.00mm_Horizontal,Connector_Generic:Conn_02x03_Odd_Even
1,F1,0.5A,Fuse:Fuse_1206_3216Metric,Device:Polyfuse
2,D1 D2,SS34,Diode_SMD:D_SMA,Diode:SS34
1,J5,power push-in,"TerminalBlock_Phoenix:TerminalBlock_Phoenix_PT-1,5-10-5.0-H_1x10_P5.00mm_Horizontal",Connector:Screw_Terminal_01x10
1,F2,10A,Fuse:Fuseholder_Blade_Mini_Keystone_3568,Device:Fuse
1,D4,SMBJ18A,Diode_SMD:D_SMB,Device:D_TVS
1,C1,47u/35V,Capacitor_SMD:C_1210_3225Metric,Device:C
1,U1,TSR 1-2450,Converter_DCDC:Converter_DCDC_TRACO_TSR-1_THT,Regulator_Switching:TSR_1-2450
2,C2 C3,22u,Capacitor_SMD:C_0805_2012Metric,Device:C
1,U2,AP7361C-33E,Package_TO_SOT_SMD:SOT-223-3_TabPin2,Regulator_Linear:AP7361C-33E
2,D3 D61,SS14,Diode_SMD:D_SMA,Diode:SS34
12,R1 R41 R42 R43 R44 R59 R106 R206 R63 R80 R83 R82,100k,Resistor_SMD:R_0603_1608Metric,Device:R
1,R2,22k,Resistor_SMD:R_0603_1608Metric,Device:R
13,C4 C6 C8 C20 C31 C32 C33 C34 C60 C90 C91 C92 C93,100n,Capacitor_SMD:C_0603_1608Metric,Device:C
1,U3,ESP32-S3-WROOM-1-N8,RF_Module:ESP32-S3-WROOM-1,RF_Module:ESP32-S3-WROOM-1
1,C5,10u,Capacitor_SMD:C_0805_2012Metric,Device:C
16,R3 R15 R16 R21 R31 R32 R33 R34 R108 R208 R61 R62 R74 R75 R76 R93,10k,Resistor_SMD:R_0603_1608Metric,Device:R
1,C7,1u,Capacitor_SMD:C_0603_1608Metric,Device:C
1,SW1,RESET,Button_Switch_SMD:SW_SPST_TL3342,Switch:SW_Push
1,SW2,BOOT,Button_Switch_SMD:SW_SPST_TL3342,Switch:SW_Push
1,J1,USB PROG,Connector_USB:USB_C_Receptacle_GCT_USB4105-xx-A_16P_TopMnt_Horizontal,Connector:USB_C_Receptacle_USB2.0_16P
2,R4 R5,5.1k,Resistor_SMD:R_0603_1608Metric,Device:R
1,U4,USBLC6-2SC6,Package_TO_SOT_SMD:SOT-23-6,Power_Protection:USBLC6-2SC6
1,D5,SK6812MINI,LED_SMD:LED_SK6812MINI_PLCC4_3.5x3.5mm_P1.75mm,LED:SK6812MINI
6,D6 D11 D12 D71 D72 D73,1N4148W,Diode_SMD:D_SOD-123,Diode:1N4148W
3,R6 R10 R11,330,Resistor_SMD:R_0603_1608Metric,Device:R
2,U5 U6,AQY212EH,Package_SO:SO-4_4.4x3.6mm_P2.54mm,Relay_SolidState:TLP3123
8,R12 R24 R58 R71 R72 R73 R90 R91,4.7k,Resistor_SMD:R_0603_1608Metric,Device:R
1,D7,4V7,Diode_SMD:D_SOD-123,Device:D_Zener
5,U7 U8 U71 U72 U73,PC817,Package_DIP:SMDIP-4_W9.53mm,Isolator:PC817
4,R13 R14 R107 R207,2.2k,Resistor_SMD:R_0603_1608Metric,Device:R
1,D8,2V4,Diode_SMD:D_SOD-123,Device:D_Zener
1,D9,green 3mm,LED_THT:LED_D3.0mm,Device:LED
1,SW3,12V ON,Button_Switch_THT:SW_PUSH-12mm,Switch:SW_Push
1,SW4,12V OFF,Button_Switch_THT:SW_PUSH-12mm,Switch:SW_Push
1,J6,ST2 FRESH,Connector_Molex:Molex_Micro-Fit_3.0_43650-0600_1x06_P3.00mm_Horizontal,Connector_Generic:Conn_01x06
3,R20 R23 R92,100,Resistor_SMD:R_0603_1608Metric,Device:R
1,F3,50mA,Fuse:Fuse_1206_3216Metric,Device:Polyfuse
6,D20 D21 D31 D32 D33 D34,ESD 5V,Diode_SMD:D_SOD-323,Device:D_TVS
1,R22,1M,Resistor_SMD:R_0603_1608Metric,Device:R
1,J7,ST3 GREY,Connector_Molex:Molex_Micro-Fit_3.0_43650-0500_1x05_P3.00mm_Horizontal,Connector_Generic:Conn_01x05
4,R30 R105 R205 R81,1k,Resistor_SMD:R_0603_1608Metric,Device:R
2,F4 F5,5A,Fuse:Fuse_1812_4532Metric,Device:Fuse
2,R50 R51,0.05 2W,Resistor_SMD:R_2512_6332Metric,Device:R
2,JP1 JP2,0R 2512 (C-feed link),Resistor_SMD:R_2512_6332Metric,Jumper:SolderJumper_2_Bridged
2,K1 K2,G5LE-1 12VDC,Relay_THT:Relay_SPDT_Omron-G5LE-1,Relay:G5LE-1
2,Q1 Q2,AO3400A,Package_TO_SOT_SMD:SOT-23,Transistor_FET:AO3400A
2,D41 D42,red,LED_SMD:LED_0603_1608Metric,Device:LED
2,U11 U21,INA180A3,Package_TO_SOT_SMD:SOT-23-5,Amplifier_Current:INA180A3
2,U12 U22,LMV331,Package_TO_SOT_SMD:SOT-23-5,Comparator:LMV331
1,J8,RJ12 Truma IN,Connector_RJ:RJ12_Amphenol_54601-x06_Horizontal,Connector:RJ12
1,J9,RJ12 Truma OUT,Connector_RJ:RJ12_Amphenol_54601-x06_Horizontal,Connector:RJ12
1,D60,PESD1LIN,Diode_SMD:D_SOD-323,Device:D_TVS
1,U60,TJA1021T/20,Package_SO:SOIC-8_3.9x4.9mm_P1.27mm,Interface_CAN_LIN:TJA1021T
2,F6 F8,1A,Fuse:Fuse_1812_4532Metric,Device:Polyfuse
1,J10,inputs push-in,"TerminalBlock_Phoenix:TerminalBlock_Phoenix_PT-1,5-4-3.5-H_1x04_P3.50mm_Horizontal",Connector:Screw_Terminal_01x04
1,JP10,JP COM,Jumper:SolderJumper-2_P1.3mm_Bridged_RoundedPad1.0x1.5mm,Jumper:SolderJumper_2_Bridged
1,F7,4A,Fuse:Fuse_1812_4532Metric,Device:Fuse
1,Q80,AO3401A,Package_TO_SOT_SMD:SOT-23,Transistor_FET:AO3401A
1,Q81,2N7002,Package_TO_SOT_SMD:SOT-23,Transistor_FET:2N7002
1,J2,PD module,Connector_PinHeader_2.54mm:PinHeader_1x02_P2.54mm_Vertical,Connector_Generic:Conn_01x02
1,U90,LIS3DH,Package_LGA:LGA-16_3x3mm_P0.5mm_LayoutBorder3x5y,Sensor_Motion:LIS3DH
1,U91,SHT40-AD1B,Sensor_Humidity:Sensirion_DFN-4_1.5x1.5mm_P0.8mm_SHT4x_NoCentralPad,Sensor_Humidity:SHT4x
1,U92,PCA9615DP,Package_SO:TSSOP-10_3x3mm_P0.5mm,io_board:PCA9615
1,J3,RJ45 EXPANSION,Connector_RJ:RJ45_Amphenol_54602-x08_Horizontal,Connector:RJ45

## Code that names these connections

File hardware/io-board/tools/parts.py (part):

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G='GND'
# ---------------- 1 power
add('J4','Connector_Generic:Conn_02x03_Odd_Even','ST1 EBL','Connector_Molex:Molex_Micro-Fit_3.0_43045-0600_2x03_P3.00mm_Horizontal',
    {'1':'EBL_OFF','2':'EBL_ON','3':'EBL_12V','4':'EBL_MAINS','5':G,'6':'ST1_12V'},'1 yellow OFF, 2 green ON, 3 white 12V-on, 4 pink mains, 5 brown GND, 6 blue +12V')
add('F1','Device:Polyfuse','0.5A 30V PTC','Fuse:Fuse_1206_3216Metric',{'1':'ST1_12V','2':'ST1_12V_F'})
D('D1','Diode:SS34','SS34','Diode_SMD:D_SMA','ST1_12V_F','V12_SYS')
add('J5','Connector:Screw_Terminal_01x04','KF2EDGR-5.0-4P','Connector_Phoenix_MSTB:PhoenixContact_MSTBA_2,5_4-G_1x04_P5.00mm_Horizontal',
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     'A6':'USB_DP','B6':'USB_DP','A7':'USB_DM','B7':'USB_DM','A8':'NC','B8':'NC'})
R('R4','5.1k','CC1_PROG',G); R('R5','5.1k','CC2_PROG',G)
add('U4','Power_Protection:USBLC6-2SC6','USBLC6-2SC6','Package_TO_SOT_SMD:SOT-23-6',{'1':'USB_DM','6':'USB_DM','3':'USB_DP','4':'USB_DP','5':'VBUS_PROG','2':G})
add('D5','LED:SK6812MINI','SK6812MINI-HS','io_board:LED_SK6812MINI-HS_3.7x3.5mm',{'4':'LED_VDD','2':G,'3':'LED_DIN','1':'NC'},'status LED, front plate; SK6812MINI (3.5 x 3.5, top mount), not the -E (3.2 x 2.8, other pinout)')
D('D6','Diode:1N4148W','1N4148W','Diode_SMD:D_SOD-123','+5V','LED_VDD')  # LED at 4.3 V so 3.3 V data meets VIH 0.7 VDD
R('R6','330','LED_DATA','LED_DIN'); C('C8','100n','LED_VDD',G)
# ---------------- 3 EBL
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    R(rr,'330',drv,ref+'_LED')
    add(ref,'Relay_SolidState:TLP3123','AQY212EH','Package_DIP:SMDIP-4_W9.53mm',{'1':ref+'_LED','2':G,'3':G,'4':line},'photoMOS, pulses the EBL line to GND (AQY212EH or TLP3123, SO-4)')
R('R12','4.7k','EBL_12V','N_12V_Z'); D('D7','Device:D_Zener','4V7','Diode_SMD:D_SOD-123','N_12V_A','N_12V_Z')
add('U7','Isolator:PC817','PC817','Package_DIP:SMDIP-4_W9.53mm',{'1':'N_12V_A','2':G,'4':'EBL_12V_SENSE','3':G})
R('R15','10k','+3V3','EBL_12V_SENSE')
R('R13','2.2k','EBL_MAINS','N_MAINS_Z'); D('D8','Device:D_Zener','2V4','Diode_SMD:D_SOD-123','N_MAINS_A','N_MAINS_Z')
add('U8','Isolator:PC817','PC817','Package_DIP:SMDIP-4_W9.53mm',{'1':'N_MAINS_A','2':G,'4':'EBL_MAINS_SENSE','3':G})
R('R16','10k','+3V3','EBL_MAINS_SENSE')
R('R14','2.2k','EBL_12V','N_LED12'); D('D9','Device:LED','green 0603','LED_SMD:LED_0603_1608Metric','N_LED12',G)  # at the front edge, light pipe
add('SW3','Switch:SW_Push','SKHHLQA010','Button_Switch_THT:SW_Tactile_SKHH_Angled',{'1':'EBL_ON','2':G},'front plate, works without the ESP32')
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    R(f'R{n}08','10k','+3V3',f'OUT{n}_SENSE')
# ---------------- 6 Truma + inputs
for ref,v in [('J8','RJ12 Truma IN'),('J9','RJ12 Truma OUT')]:
    add(ref,'Connector:RJ12','DS1133-S60BPX','io_board:RJ12_Connfly_DS1133-S60_Horizontal',{'1':'TR1','2':'TR2','3':'LIN','4':'TR4','5':G,'6':'TR6'},'pin 3 LIN, 5 GND (inetbox.py), others 1:1')
add('D60','Device:D_TVS','PESD1LIN','Diode_SMD:D_SOD-323',{'1':'LIN','2':G})
D('D61','Diode:SS34','SS14','Diode_SMD:D_SMA','V12_SYS','LIN_VBAT')
C('C60','100n','LIN_VBAT',G)
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for k in (1,2,3):
    D(f'D7{k}','Diode:1N4148W','1N4148W','Diode_SMD:D_SOD-123',f'IN{k}_T',f'IN{k}_D')
    R(f'R7{k}','4.7k 0.25W',f'IN{k}_D',f'IN{k}_A','Resistor_SMD:R_1206_3216Metric')  # 30 V: 169 mW
    add(f'U7{k}','Isolator:PC817','PC817','Package_DIP:SMDIP-4_W9.53mm',{'1':f'IN{k}_A','2':'IN_COM','4':f'IN{k}','3':G})
    R(f'R7{k+3}','10k','+3V3',f'IN{k}')
# ---------------- 7 USB PD module, sensors, expansion
add('F7','Device:Fuse','4A 0451004.MRL','Fuse:Fuse_Littelfuse-NANO2-451_453',{'1':'V12_AUX','2':'PD_SUPPLY'})
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add('Q81','Transistor_FET:2N7002','2N7002','Package_TO_SOT_SMD:SOT-23',{'3':'PD_G_DRV','2':G,'1':'PD_EN_G'})
R('R83','100k','PD_G_DRV','PD_G')  # with R80: VGS = -V/2, inside AO3401A +-12 V
R('R81','1k','USB_PD_EN','PD_EN_G'); R('R82','100k','PD_EN_G',G)
add('J2','Connector_Generic:Conn_01x02','PD module','Connector_PinHeader_2.54mm:PinHeader_1x02_P2.54mm_Vertical',{'1':'PD_12V','2':G},'ready-made 12 V to USB-C PD 30 W module, its socket in the front plate')
R('R90','4.7k','+3V3','SDA'); R('R91','4.7k','+3V3','SCL'); R('R93','10k','+3V3','EXP_INT_MCU')
add('U90','Sensor_Motion:LIS3DH','LIS3DH','Package_LGA:LGA-16_3x3mm_P0.5mm_LayoutBorder3x5y',
    {'1':'+3V3','14':'+3V3','5':G,'10':G,'12':G,'4':'SCL','6':'SDA','7':G,'8':'+3V3','11':'TILT_INT','9':'NC','13':'NC','15':'NC','16':'NC','2':'NC','3':'NC'},'tilt, I2C 0x18 (LIS2DH12 is LGA-12 2x2, not this footprint)')
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C('C92','100n','+3V3',G); C('C93','100n','+5V',G)
add('F8','Device:Polyfuse','1A 30V PTC','Fuse:Fuse_1812_4532Metric',{'1':'V12_AUX','2':'EXP_12V'})
R('R92','100','EXP_INT_MCU','EXP_INT')  # expansion interrupt: open drain on the module side, own GPIO
# dI2C termination + idle bias at this end of the cable (NXP PCA9615 Fig. 5/7: 600-120-600 at VDD(B) 5 V)
for (pp,mm,ra,rb,rc) in (('DSCL_P','DSCL_M','R94','R95','R96'),('DSDA_P','DSDA_M','R97','R98','R99')):
    R(ra,'620','+5V',pp); R(rb,'120',pp,mm); R(rc,'620',mm,G)
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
